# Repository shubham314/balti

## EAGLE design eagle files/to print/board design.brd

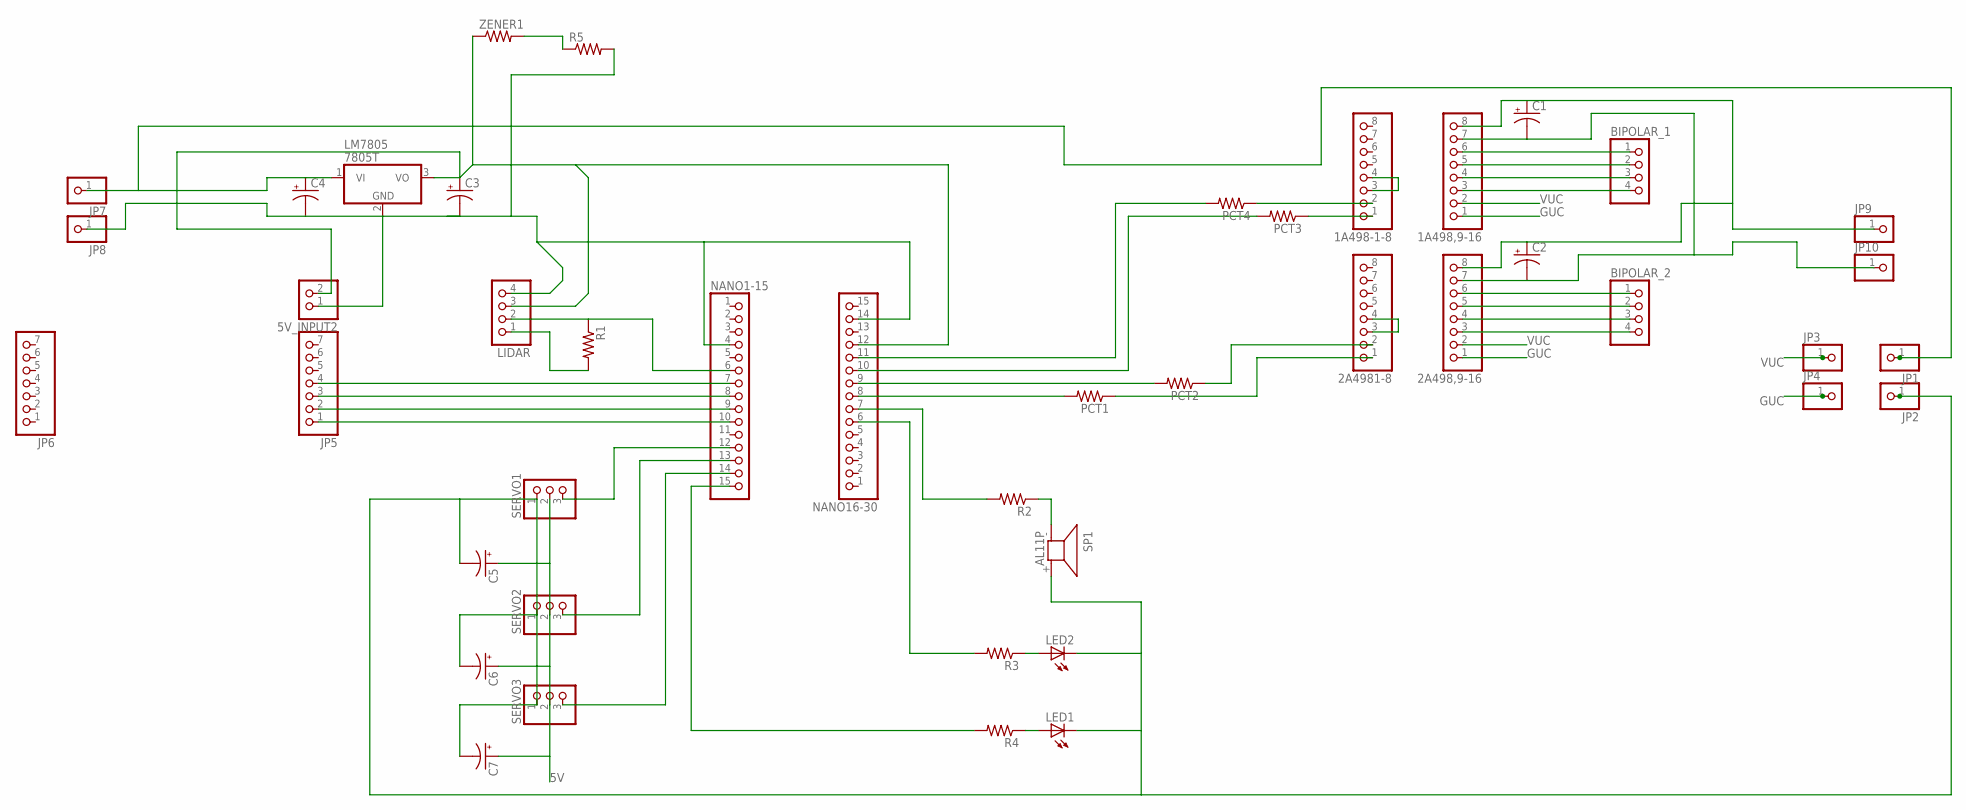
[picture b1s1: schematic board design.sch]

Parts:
1A498,9-16, 1A498-1-8, 2A498,9-16, 2A4981-8: PINHD-1X8; 1X08
5V_INPUT2: PINHD-1X2; 1X02
BIPOLAR_1, BIPOLAR_2: PINHD-1X4; 1X04
C1, C2, C3, C4, C5, C6, C7: CPOL-USE2.5-7; E2,5-7
JP1, JP2, JP3, JP4, JP7, JP8, JP9, JP10: PINHD-1X1; 1X01
JP5, JP6: PINHD-1X7; 1X07
LED1, LED2: LED5MM
LIDAR: PINHD-1X4; 1X04
LM7805: 7805T; TO220H
NANO1-15, NANO16-30: PINHD-1X15; 1X15
PCT1, PCT2, PCT3, PCT4: R-US_0207/10; 0207/10
R1, R2, R3, R4, R5: R-US_0207/10; 0207/10
SERVO1, SERVO2, SERVO3: PINHD-1X3; 1X03
SP1: AL11P
ZENER1: R-US_0207/10; 0207/10

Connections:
5V: C4.+, C5.+, C6.+, C7.+, JP1.1, JP7.1, LM7805.1 (VI), SERVO1.2, SERVO2.2, SERVO3.2
GUC: 1A498,9-16.1, 2A498,9-16.1, JP4.1
unnamed: JP5.4, NANO1-15.7
unnamed: JP5.3, NANO1-15.8
unnamed: JP5.2, NANO1-15.9
unnamed: JP5.1, NANO1-15.10
unnamed: NANO16-30.7, R2.2
unnamed: LED2.A, R3.1
unnamed: 1A498-1-8.2, PCT4.1
unnamed: NANO16-30.8, PCT1.2
unnamed: 2A498,9-16.6, BIPOLAR_2.1
unnamed: 2A498,9-16.5, BIPOLAR_2.2
unnamed: 2A498,9-16.4, BIPOLAR_2.3
unnamed: 2A498,9-16.3, BIPOLAR_2.4
unnamed: 1A498,9-16.6, BIPOLAR_1.1
unnamed: 1A498,9-16.5, BIPOLAR_1.2
unnamed: 1A498,9-16.4, BIPOLAR_1.3
unnamed: 1A498,9-16.3, BIPOLAR_1.4
unnamed: LED1.A, R4.1
unnamed: NANO1-15.15, R4.2
unnamed: R2.1, SP1.- (1)
unnamed: LIDAR.2, NANO1-15.6, R1.1
unnamed: LIDAR.1, R1.2
unnamed: 1A498,9-16.7, 2A498,9-16.7, C1.-, C2.-, JP10.1
unnamed: 2A4981-8.3, 2A4981-8.4
unnamed: 1A498-1-8.3, 1A498-1-8.4
unnamed: 1A498,9-16.8, 2A498,9-16.8, C1.+, C2.+, JP9.1
unnamed: NANO1-15.12, SERVO1.3
unnamed: NANO1-15.13, SERVO2.3
unnamed: NANO1-15.14, SERVO3.3
unnamed: NANO16-30.11, PCT4.2
unnamed: NANO16-30.10, PCT3.2
unnamed: NANO16-30.9, PCT2.2
unnamed: 2A4981-8.1, PCT1.1
unnamed: NANO16-30.6, R3.2
unnamed: 2A4981-8.2, PCT2.1
unnamed: 1A498-1-8.1, PCT3.1
unnamed: C5.-, C6.-, C7.-, JP2.1, LED1.K (C), LED2.K (C), SERVO1.1, SERVO2.1, SERVO3.1, SP1.+ (2)
unnamed: 5V_INPUT2.2, C3.+, LIDAR.3, LM7805.3 (VO), NANO16-30.12, ZENER1.1
unnamed: 5V_INPUT2.1, C3.-, C4.-, JP8.1, LIDAR.4, LM7805.2 (GND), NANO1-15.4, NANO16-30.14, R5.2
unnamed: R5.1, ZENER1.2
VUC: 1A498,9-16.2, 2A498,9-16.2, JP3.1

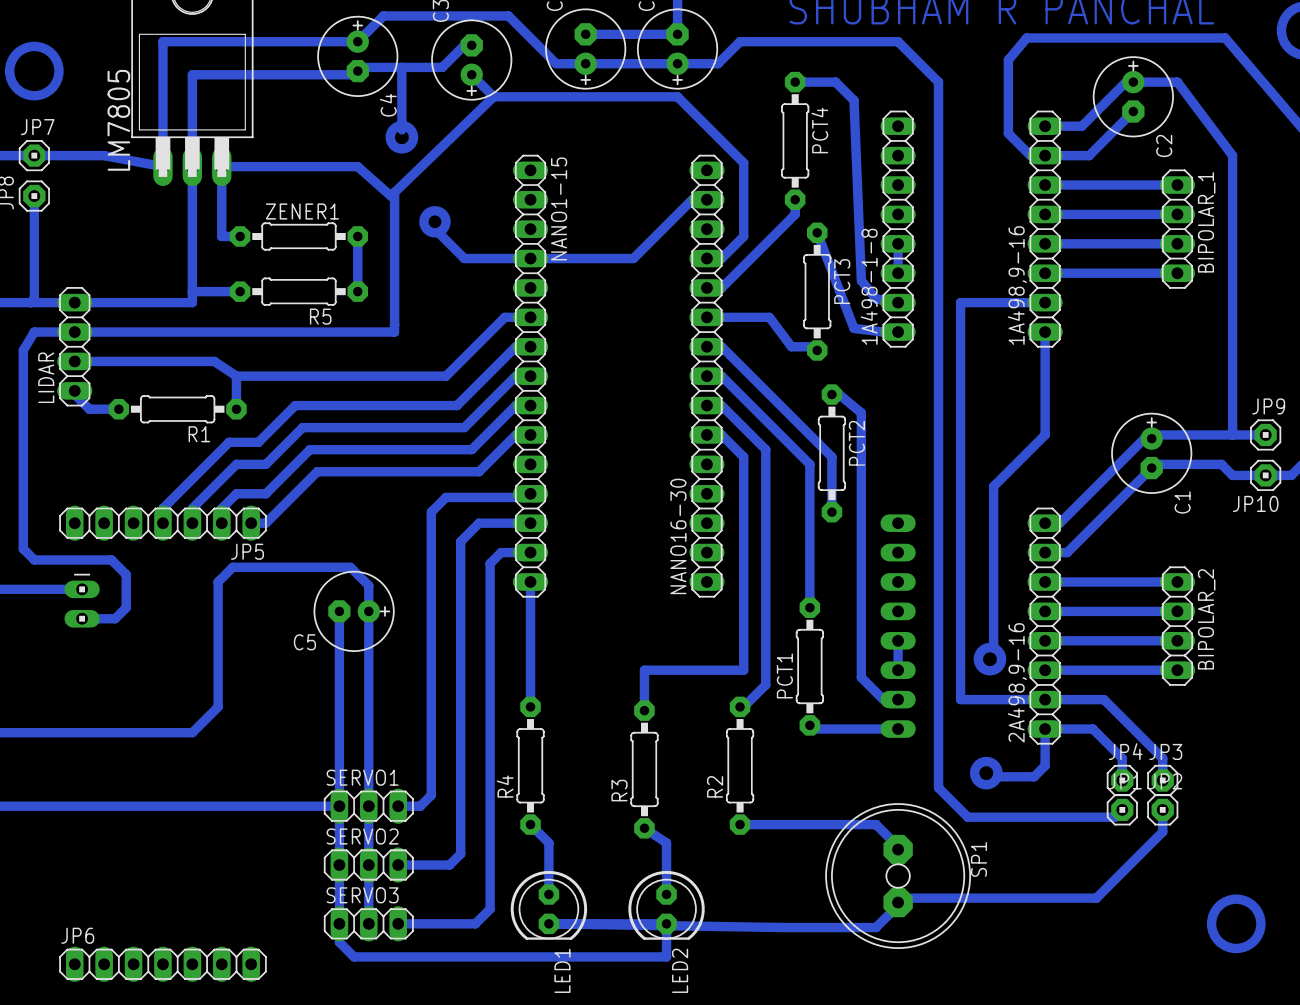
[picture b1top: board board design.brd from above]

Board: 2 copper layers, 44 parts (1 on the bottom side), 42 nets.

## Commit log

2019-02-10 10/2/19
2019-02-10 10/2/19 -2
2019-02-12 12/2/19
2019-02-15 first backup 15-2-18
2019-02-23 first codes added for balti
2019-02-23 python references added
2019-03-05 build 5_3_19 added
2019-03-07 arduino code build 7_3_2019
2019-03-11 vpython serial code build_1
2019-03-17 vpython 3d code completed
2019-06-16 new start
2019-06-16 see this
2020-04-07 revision

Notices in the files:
parts and their libraries:
uln2003: Released under the Creative Commons Attribution 4.0 International License: http://creativecommons.org/licenses/by/4.0
